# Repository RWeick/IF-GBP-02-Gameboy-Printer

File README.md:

# IF-GBP-02-Gameboy-Printer
The full schematic and gerbers for the Nintendo Gameboy Printer PCB revision 02

This schematic is verified to be 100% complete and accurate.

PCB Thickness: 1.2 mm

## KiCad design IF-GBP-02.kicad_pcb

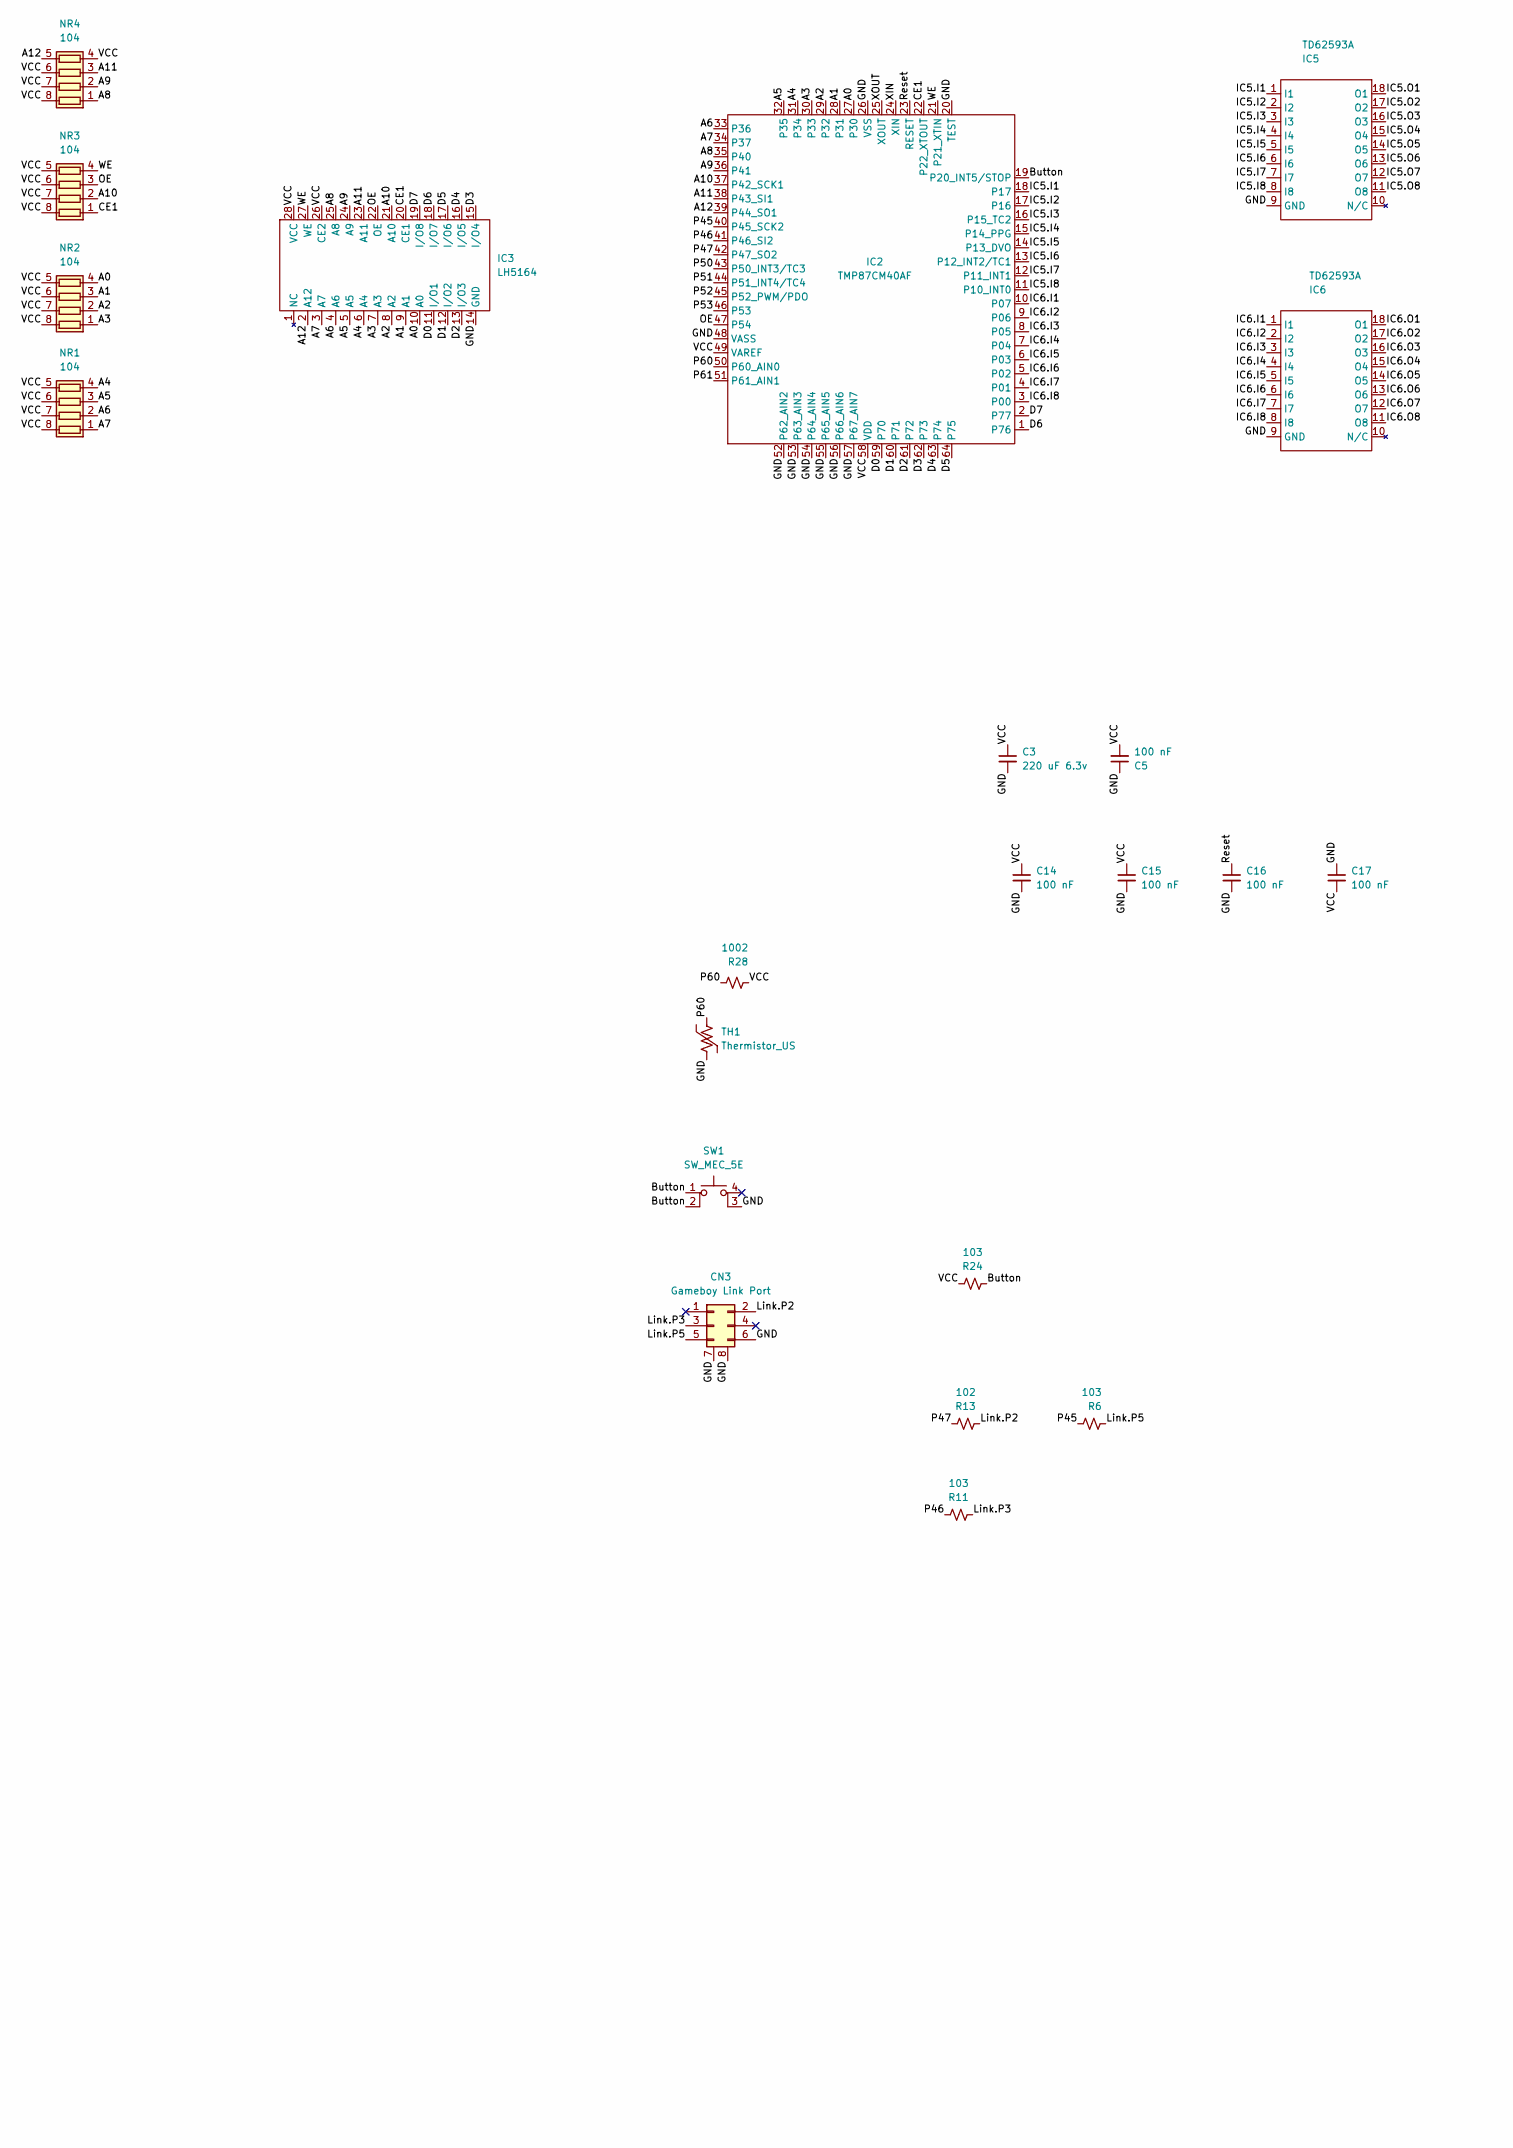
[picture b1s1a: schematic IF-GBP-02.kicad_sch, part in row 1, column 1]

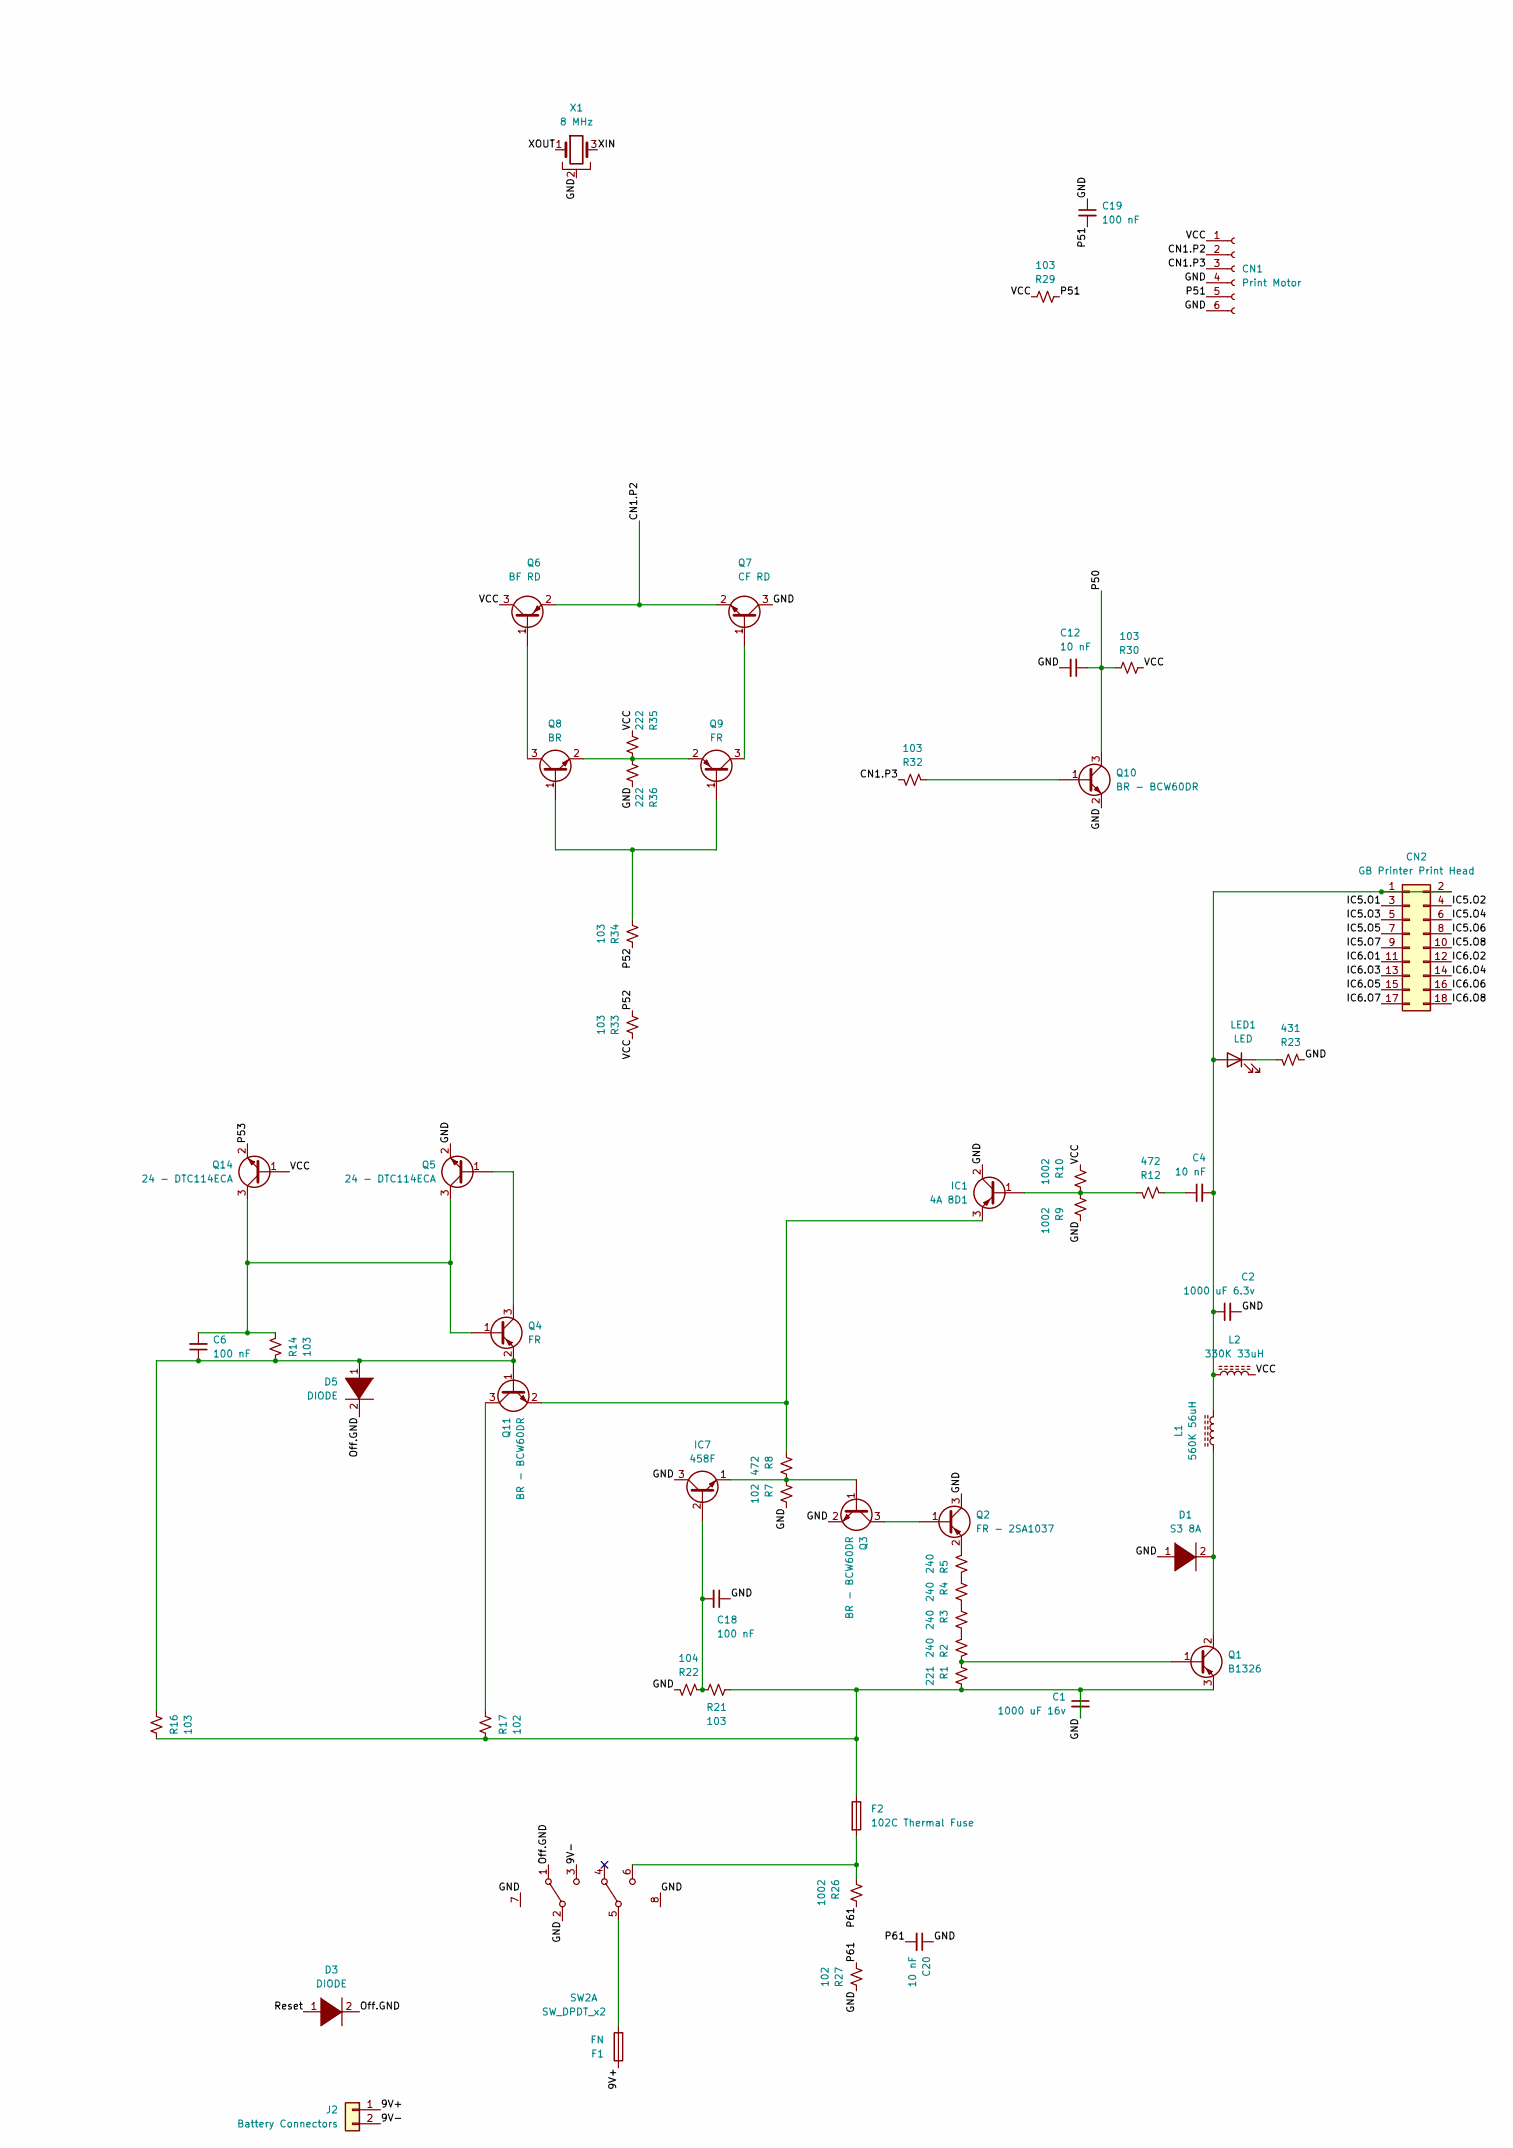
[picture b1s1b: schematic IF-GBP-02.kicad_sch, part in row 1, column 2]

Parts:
C1: 1000 uF 16v; C1 1000 uF Cap
C2: 1000 uF 6.3v; C2 1000 uF Cap
C3: 220 uF 6.3v; C3 220 uF Cap
C4, C12, C20: 10 nF; SMD Cap-Res
C5, C6, C14, C15, C16, C17, C18, C19: 100 nF; SMD Cap-Res
CN1: Print Motor; Printer Motor Connector
CN2: GB Printer Print Head; Printer Head Connector
CN3: Gameboy Link Port
D1: S3 8A; D1 Diode
D3, D5: DIODE; Little Diode
F1: FN; F1 Fuse
F2: 102C Thermal Fuse; F2 Thermal Fuse
IC1: 4A 8D1; SOT89 Transistor
IC2: TMP87CM40AF
IC3: LH5164; LH5164 SRAM
IC5, IC6: TD62593A
IC7: 458F; SOT23-5 Transistor
J2: Battery Connectors
L1: 560K 56uH; L1 Inductor
L2: 330K 33uH; L2 Inductor
LED1: LED
NR1, NR2, NR3, NR4: 104; Resistor Pack
Q1: B1326
Q2: FR - 2SA1037; Transistor
Q3, Q10, Q11: BR - BCW60DR; Transistor
Q4, Q9: FR; Transistor
Q5, Q14: 24 - DTC114ECA; Transistor
Q6: BF RD; SOT89 Transistor
Q7: CF RD; SOT89 Transistor
Q8: BR; Transistor
R1: 221; SMD Cap-Res
R2, R3, R4, R5: 240; SMD Cap-Res
R6, R11, R14, R16, R21, R24, R29, R30, R32, R33, R34: 103; SMD Cap-Res
R7, R13, R17, R27: 102; SMD Cap-Res
R8, R12: 472; SMD Cap-Res
R9, R10, R26, R28: 1002; SMD Cap-Res
R22: 104; SMD Cap-Res
R23: 431; SMD Cap-Res
R35, R36: 222; SMD Cap-Res
SW1: SW_MEC_5E; Feed Button
SW2: SW_DPDT_x2; Slide Switch
TH1: Thermistor_US; TH1 Thermistor
X1: 8 MHz; 8 MHz Crystal

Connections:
/9V+: F1.1, J2.1
/9V-: J2.2, SW2.3 (C)
/9V.F1: F1.2, SW2.5 (B)
/9V.Prefuse: F2.2, R26.2, SW2.6 (C)
/A0: IC2.27 (P30), IC3.10 (A0), NR2.4 (R4.1)
/A1: IC2.28 (P31), IC3.9 (A1), NR2.3 (R3.1)
/A2: IC2.29 (P32), IC3.8 (A2), NR2.2 (R2.1)
/A3: IC2.30 (P33), IC3.7 (A3), NR2.1 (R1.1)
/A4: IC2.31 (P34), IC3.6 (A4), NR1.4 (R4.1)
/A5: IC2.32 (P35), IC3.5 (A5), NR1.3 (R3.1)
/A6: IC2.33 (P36), IC3.4 (A6), NR1.2 (R2.1)
/A7: IC2.34 (P37), IC3.3 (A7), NR1.1 (R1.1)
/A8: IC2.35 (P40), IC3.25 (A8), NR4.1 (R1.1)
/A9: IC2.36 (P41), IC3.24 (A9), NR4.2 (R2.1)
/A10: IC2.37 (P42_SCK1), IC3.21 (A10), NR3.2 (R2.1)
/A11: IC2.38 (P43_SI1), IC3.23 (A11), NR4.3 (R3.1)
/A12: IC2.39 (P44_SO1), IC3.2 (A12), NR4.5 (R4.2)
/Button: IC2.19 (P20_INT5/STOP), R24.2, SW1.1, SW1.2
/CE1: IC2.22 (P22_XTOUT), IC3.20 (CE1), NR3.1 (R1.1)
/CN1.P2: CN1.2, Q6.2 (VIN), Q7.2 (E)
/CN1.P3: CN1.3, R32.2
/D0: IC2.59 (P70), IC3.11 (I/O1)
/D1: IC2.60 (P71), IC3.12 (I/O2)
/D2: IC2.61 (P72), IC3.13 (I/O3)
/D3: IC2.62 (P73), IC3.15 (I/O4)
/D4: IC2.63 (P74), IC3.16 (I/O5)
/D5: IC2.64 (P75), IC3.17 (I/O6)
/D6: IC2.1 (P76), IC3.18 (I/O7)
/D7: IC2.2 (P77), IC3.19 (I/O8)
/IC5.I1: IC2.18 (P17), IC5.1 (I1)
/IC5.I2: IC2.17 (P16), IC5.2 (I2)
/IC5.I3: IC2.16 (P15_TC2), IC5.3 (I3)
/IC5.I4: IC2.15 (P14_PPG), IC5.4 (I4)
/IC5.I5: IC2.14 (P13_DVO), IC5.5 (I5)
/IC5.I6: IC2.13 (P12_INT2/TC1), IC5.6 (I6)
/IC5.I7: IC2.12 (P11_INT1), IC5.7 (I7)
/IC5.I8: IC2.11 (P10_INT0), IC5.8 (I8)
/IC5.O1: CN2.3, IC5.18 (O1)
/IC5.O2: CN2.4, IC5.17 (O2)
/IC5.O3: CN2.5, IC5.16 (O3)
/IC5.O4: CN2.6, IC5.15 (O4)
/IC5.O5: CN2.7, IC5.14 (O5)
/IC5.O6: CN2.8, IC5.13 (O6)
/IC5.O7: CN2.9, IC5.12 (O7)
/IC5.O8: CN2.10, IC5.11 (O8)
/IC6.I1: IC2.10 (P07), IC6.1 (I1)
/IC6.I2: IC2.9 (P06), IC6.2 (I2)
/IC6.I3: IC2.8 (P05), IC6.3 (I3)
/IC6.I4: IC2.7 (P04), IC6.4 (I4)
/IC6.I5: IC2.6 (P03), IC6.5 (I5)
/IC6.I6: IC2.5 (P02), IC6.6 (I6)
/IC6.I7: IC2.4 (P01), IC6.7 (I7)
/IC6.I8: IC2.3 (P00), IC6.8 (I8)
/IC6.O1: CN2.11, IC6.18 (O1)
/IC6.O2: CN2.12, IC6.17 (O2)
/IC6.O3: CN2.13, IC6.16 (O3)
/IC6.O4: CN2.14, IC6.15 (O4)
/IC6.O5: CN2.15, IC6.14 (O5)
/IC6.O6: CN2.16, IC6.13 (O6)
/IC6.O7: CN2.17, IC6.12 (O7)
/IC6.O8: CN2.18, IC6.11 (O8)
/LED.Anode: C2.1, C4.2, CN2.1, CN2.2, L1.1, L2.1, LED1.2 (A)
/LED.Cathode: LED1.1 (K), R23.2
/Link.P2: CN3.2, R13.2
/Link.P3: CN3.3, R11.2
/Link.P5: CN3.5, R6.2
/OE: IC2.47 (P54), IC3.22 (OE), NR3.3 (R3.1)
/Off.GND: D3.2 (A), D5.2 (A), SW2.1 (A)
/P45: IC2.40 (P45_SCK2), R6.1
/P46: IC2.41 (P46_SI2), R11.1
/P47: IC2.42 (P47_SO2), R13.1
/P50: C12.1, IC2.43 (P50_INT3/TC3), Q10.3 (C), R30.1
/P51: C19.2, CN1.5, IC2.44 (P51_INT4/TC4), R29.2
/P52: IC2.45 (P52_PWM/PDO), R33.2, R34.1
/P53: IC2.46 (P53), Q14.2 (E)
/P60: IC2.50 (P60_AIN0), R28.1, TH1.1
/P61: C20.2, IC2.51 (P61_AIN1), R26.1, R27.2
/Reset: C16.1, D3.1 (K), IC2.23 (RESET)
/Route1: D1.2 (A), L1.2, Q1.2 (C)
/Route2: Q1.1 (B), R1.2, R2.2
/Route3: R2.1, R3.1
/Route4: R3.2, R4.1
/Route5: R4.2, R5.2
/Route6: Q2.2 (E), R5.1
/Route7: Q2.1 (B), Q3.3 (C)
/Route8: IC1.1 (B), R9.2, R10.1, R12.2
/Route9: C4.1, R12.1
/Route12: Q7.1 (B), Q9.3 (C)
/Route13: Q8.1 (B), Q9.1 (B), R34.2
/Route14: Q8.2 (E), Q9.2 (E), R35.1, R36.2
/Route15: IC1.3 (+), Q11.2 (E), R8.2
/Route16: Q6.1 (GND), Q8.3 (C)
/Route19: C6.1, D5.1 (K), Q4.2 (E), Q11.1 (B), R14.1, R16.1
/Route20: IC7.1 (E), Q3.1 (B), R7.2, R8.1
/Route21: C18.2, IC7.2 (B), R21.2, R22.1
/Route23: C6.2, Q4.1 (B), Q5.3 (C), Q14.3 (C), R14.2
/Route24: Q4.3 (C), Q5.1 (B)
/Route25: Q11.3 (C), R17.1
/Route27: Q10.1 (B), R32.1
/VCC: C3.1, C5.2, C14.1, C15.1, C17.2, CN1.1, IC2.49 (VAREF), IC2.58 (VDD), IC3.26 (CE2), IC3.28 (VCC), L2.2, NR1.5 (R4.2), NR1.6 (R3.2), NR1.7 (R2.2), NR1.8 (R1.2), NR2.5 (R4.2), NR2.6 (R3.2), NR2.7 (R2.2), NR2.8 (R1.2), NR3.5 (R4.2), NR3.6 (R3.2), NR3.7 (R2.2), NR3.8 (R1.2), NR4.4 (R4.1), NR4.6 (R3.2), NR4.7 (R2.2), NR4.8 (R1.2), Q6.3 (VOUT), Q14.1 (B), R10.2, R24.1, R28.2, R29.1, R30.2, R33.1, R35.2
/WE: IC2.21 (P21_XTIN), IC3.27 (WE), NR3.4 (R4.1)
/XIN: IC2.24 (XIN), X1.3
/XOUT: IC2.25 (XOUT), X1.1

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
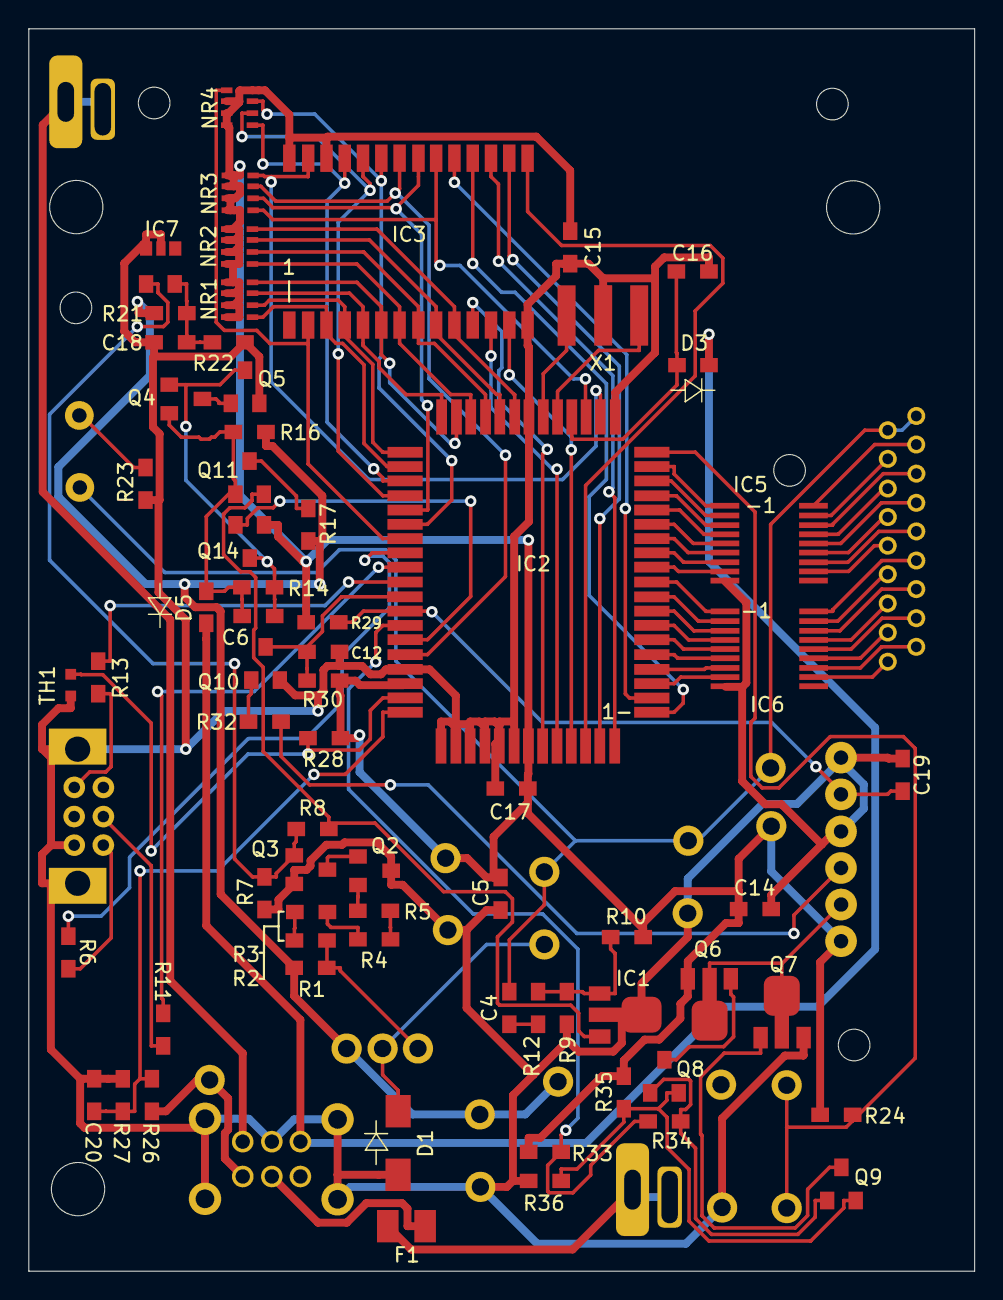
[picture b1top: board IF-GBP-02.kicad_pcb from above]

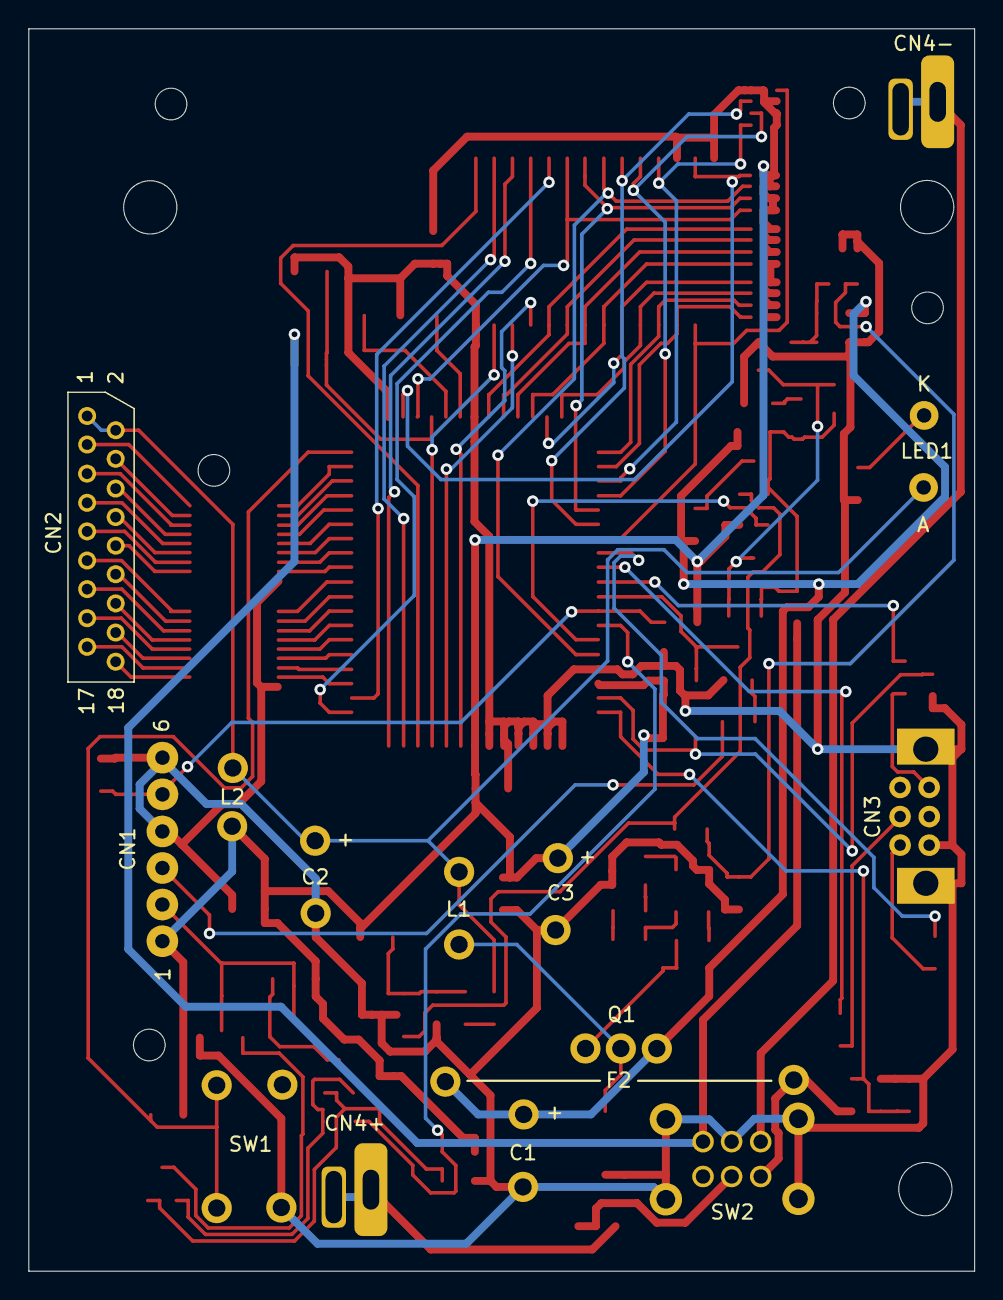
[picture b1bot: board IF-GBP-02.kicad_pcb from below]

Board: 2 copper layers, 65.7 x 86.3 mm, 93 parts (21 on the bottom side), 105 nets.

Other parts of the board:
D1Diagram, D3Diagram, D5Diagram: 867ee1a9-3078-458d-9784-2b6d66f4ccf8
Hole1, Hole5, Hole7: MountingHole_2.2mm_M2_ISO7380
Hole2, Hole4, Hole6: MountingHole_3.7mm
Hole3, Hole8: MountingHole_2.2mm_M2

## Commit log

2022-09-23 Add files via upload
    Updated PCB with corrected traces
